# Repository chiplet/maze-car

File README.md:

# maze-car
This repository contains the example code for the Mazeblazer game. 

The full game instructions and a more detailed getting started guide are available at:
https://docs.google.com/document/d/1SaZNl0VVnFEm_aR2c8GMJGQdpziAJxaRw1_wqC6xl4o/edit?usp=sharing

## Getting Started
1. Download the code from this repository to your computer
- Download git for windows/linux/macOS from https://git-scm.com/downloads
- Use command `git clone https://github.com/VerkkuUkkeli/maze-car` to download a copy of the repository to your machine
2. Download and install the Arduino IDE from https://www.arduino.cc/en/Main/Software
3. Install the following Arduino libraries from Sketch -> Include Library -> Manage Libraries menu in the arduino IDE
- Adafruit Unified Sensor
- Adafruit LSM303DLHC
4. Tell the Arduino IDE what board is being used from the Tools menu
- Board: Arduino Nano
- Processor: ATmega328P (Old Bootloader)
- Port: wchusbserial

## Software
- `main.ino` contains the arduino setup and loop code. Write your maze solving application into this file.
- `helpers.ino` contains helper functions for interfacing with the car hardware.

## Hardware
The provided code already takes care of interfacing with the hardware. If you for whatever reason want to write code for interfacing with the hardware directly you are welcome to do so. The components used in the car are listed below.

- Arduino Nano
- Motor driver - [TB6612FNG](https://learn.sparkfun.com/tutorials/tb6612fng-hookup-guide)
- 2 motors
- 5 custom IR distance sensors
- Magnetometer - LSM303DLHC

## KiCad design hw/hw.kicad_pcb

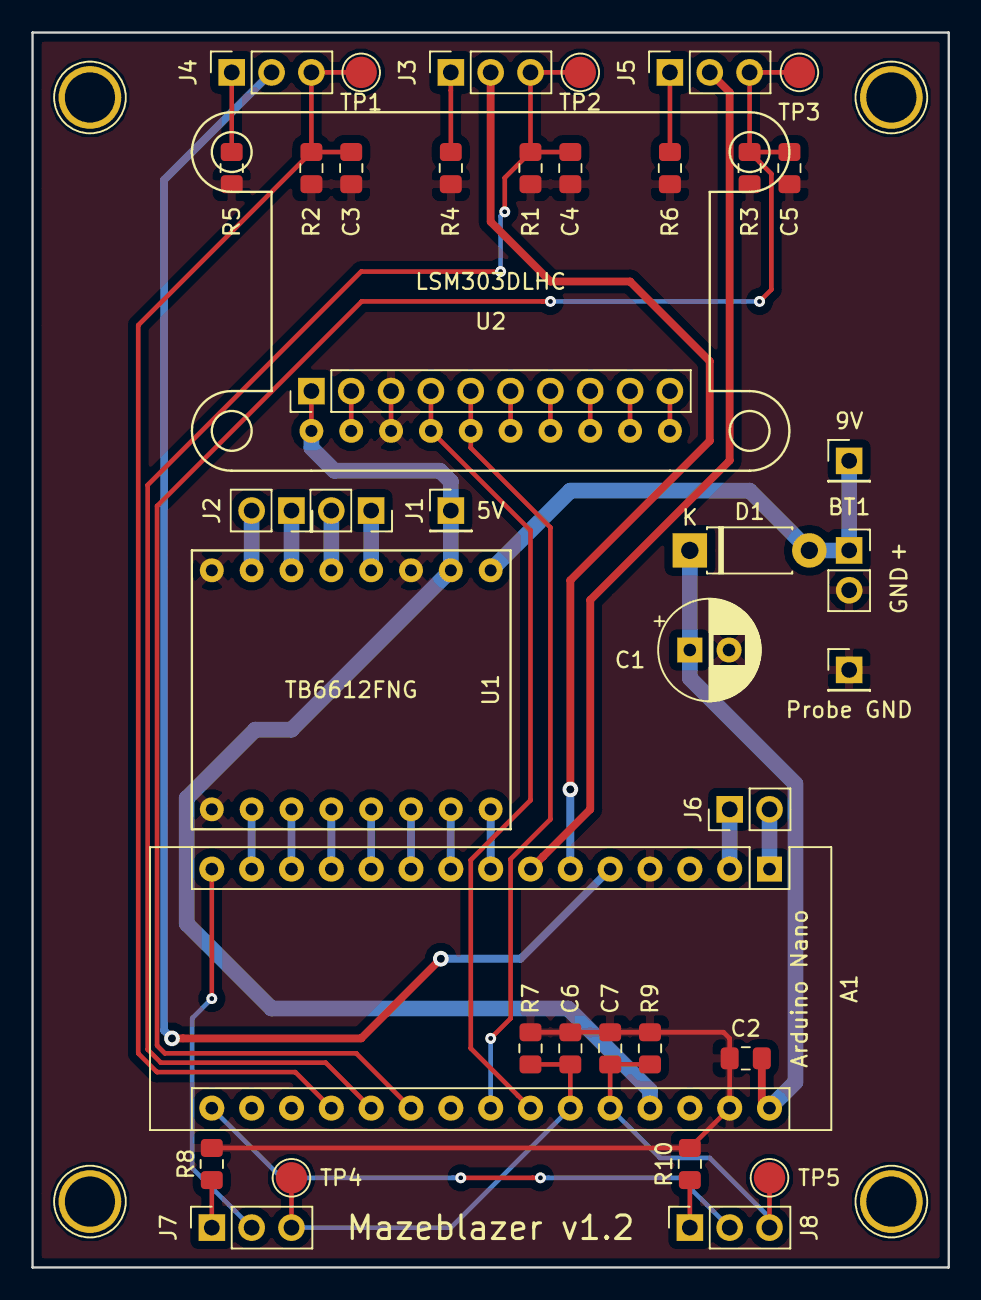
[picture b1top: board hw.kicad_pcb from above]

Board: 2 copper layers, 58.4 x 78.7 mm, 36 parts (0 on the bottom side), 34 nets.

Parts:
5V: PinHeader_1x01_P2.54mm_Vertical
A1: Arduino_Nano_v3.x; Arduino_Nano
BT1: Battery; PinSocket_1x02_P2.54mm_Vertical
C1: 100u; CP_Radial_D6.3mm_P2.50mm
C2, C3, C4, C5, C6, C7: 100n; C_0805_2012Metric_Pad1.15x1.40mm_HandSolder
D1: 1N5817; D_DO-41_SOD81_P7.62mm_Horizontal
J1: M1; PinSocket_1x02_P2.54mm_Vertical
J2: M2; PinSocket_1x02_P2.54mm_Vertical
J3: sensor 2; PinSocket_1x03_P2.54mm_Vertical
J4: sensor 1; PinSocket_1x03_P2.54mm_Vertical
J5: sensor 3; PinSocket_1x03_P2.54mm_Vertical
J6: TX/RX; PinHeader_1x02_P2.54mm_Vertical
J7: sensor 4; PinSocket_1x03_P2.54mm_Vertical
J8: sensor 5; PinSocket_1x03_P2.54mm_Vertical
R1, R2, R3, R7, R9: 1M; R_0805_2012Metric_Pad1.15x1.40mm_HandSolder
R4, R5, R6, R8, R10: 330; R_0805_2012Metric_Pad1.15x1.40mm_HandSolder
TP1, TP2, TP3, TP4, TP5: TestPoint_Pad_D2.0mm
U1: TB6612FNG_Breakout; TB6612FNG breakout
U2: L3GD20_breakout

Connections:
+5V: 5V.1, A1.27, U1.2, U2.1
+9V: BT1.1, D1.2, U1.1
GND: A1.4, A1.29, BT1.2, C1.2, C2.2, C3.2, C4.2, C5.2, C6.2, C7.2, R1.1, R2.1, R3.1, R4.2, R5.2, R6.2, R7.1, R8.2, R9.1, R10.2, U1.3, U1.8, U1.9, U2.3
IMU_SCL: A1.24, U2.4
IMU_SDA: A1.23, U2.5
unnamed: A1.1, J6.2
unnamed: A1.2, J6.1
unnamed: A1.8, U1.16
unnamed: A1.9, U1.15
unnamed: A1.10, U1.14
unnamed: A1.11, U1.13
unnamed: A1.12, U1.12
unnamed: A1.13, U1.11
unnamed: A1.14, U1.10
unnamed: J1.1, U1.4
unnamed: J1.2, U1.5
unnamed: J2.1, U1.6
unnamed: J2.2, U1.7
unnamed: J3.1, R4.1
unnamed: J4.1, R5.1
unnamed: J5.1, R6.1
unnamed: J7.1, R8.1
unnamed: J8.1, R10.1
V_a: A1.30, C1.1, C2.1, D1.1
dist-led-1: A1.5, J4.2
dist-led-2: A1.6, J3.2
dist-led-3: A1.7, J5.2
dist-led-4: A1.15, J7.2
dist-led-5: A1.16, J8.2
dist-sig-1: A1.19, C3.1, J4.3, R2.2, TP1.1
dist-sig-2: A1.20, C4.1, J3.3, R1.2, TP2.1
dist-sig-3: A1.21, C5.1, J5.3, R3.2, TP3.1
dist-sig-4: A1.25, C6.1, J7.3, R7.2, TP4.1
dist-sig-5: A1.26, C7.1, J8.3, R9.2, TP5.1

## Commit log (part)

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2019-03-05 Added motor control test script
2019-03-06 Added sensor connectors
2019-03-06 Added resistors for distance sensors. Added motor driver and shift register for more output
2019-03-06 Saved schematic file
2019-03-08 Laid out PCB footprints
2019-03-11 Modified pads
2019-03-12 Added helper function for driving motors
2019-04-01 Added small self driving demo
2019-04-01 Remote control demo
2019-04-01 Added bluetooth controller code
2019-04-16 new pcb version
2019-05-01 Added PCB v1.2
2019-05-03 README.md
2019-05-03 Modified software to support sensors for the new hardware
2019-05-03 Added magnetometer code
2019-05-05 minor changes
2019-05-05 Removed unnecessary files. Renamed main directory to source
2019-05-06 cleaned up README
2019-05-06 Renamed source directory back to main
2019-05-07 Prepared code for user testing
2019-05-07 Improved getting started instructions
2019-05-08 fixed sensor index typo
2024-03-17 minor tweak
2024-03-17 own attempt at maze control sw
